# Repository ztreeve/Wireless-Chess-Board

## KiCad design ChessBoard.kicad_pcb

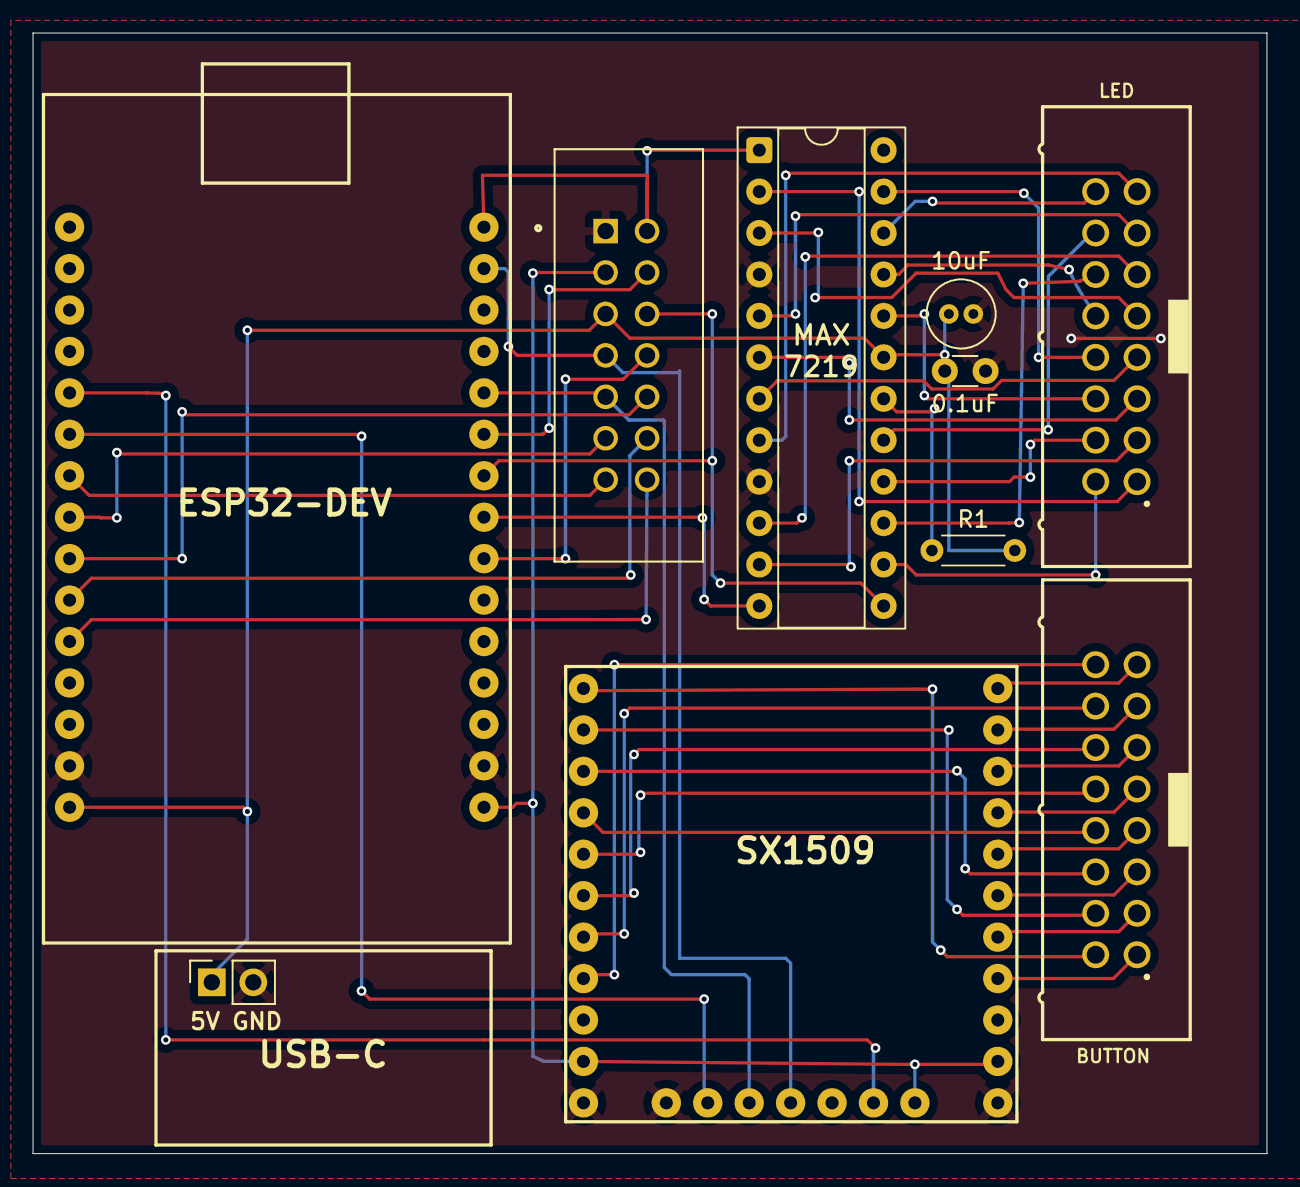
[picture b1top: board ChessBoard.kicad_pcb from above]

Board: 2 copper layers, 75.6 x 68.7 mm, 10 parts (0 on the bottom side), 50 nets.

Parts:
0.1uF: 0.1uF; C_Disc_D3.0mm_W1.6mm_P2.50mm
10uF: 10uF; C_Radial_D4.0mm_H5.0mm_P1.50mm
BUTTON: 16PIN HEADER; 61201621621
J1: SBH11-PBPC-D07-ST-BK; SULLINS_SBH11-PBPC-D07-ST-BK
J2: 6120XX21621_61201621621; 61201621621
J3: USBC BREAKOUT PINS; PinSocket_1x02_P2.54mm_Vertical
R1: 17k; R_Axial_DIN0204_L3.6mm_D1.6mm_P5.08mm_Horizontal
U1: ESP32_DEVKIT_V1_30PIN
U2: SX1509 BREAKOUT
U3: MAX7219; DIP-24_W7.62mm_Socket

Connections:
+3V3: J1.3, U1.1 (3V3), U2.18 (3.3V3), U2.26 (3.3V2), U2.28 (3.3V)
+5V: 0.1uF.1, 10uF.1, J1.5, J3.1, R1.2, U1.30 (VIN), U3.19 (V+)
/A0: BUTTON.1, U2.1 (0)
/A1: BUTTON.3, U2.2 (1)
/A2: BUTTON.5, U2.3 (2)
/A3: BUTTON.7, U2.4 (3)
/A4: BUTTON.9, U2.5 (4)
/A5: BUTTON.11, U2.6 (5)
/A6: BUTTON.13, U2.7 (6)
/A7: BUTTON.15, U2.8 (7)
/B0: BUTTON.2, U2.9 (8)
/B1: BUTTON.4, U2.10 (9)
/B2: BUTTON.6, U2.11 (10)
/B3: BUTTON.8, U2.12 (11)
/B4: BUTTON.10, U2.13 (12)
/B5: BUTTON.12, U2.14 (13)
/B6: BUTTON.14, U2.15 (14)
/B7: BUTTON.16, U2.16 (15)
/CLK: J1.6, U1.9 (D18), U3.13 (CLK)
/CS_1: U1.8 (D5), U3.12 (LOAD)
/CS_2: J1.8, U1.7 (D17)
/D14: J1.14, U1.26 (D14)
/D25: J1.11, U1.23 (D25)
/D26: J1.10, U1.24 (D26)
/D27: J1.12, U1.25 (D27)
/D33: J1.13, U1.22 (D33)
/DIG0: J2.1, U3.2 (DIG_0)
/DIG1: J2.3, U3.11 (DIG_1)
/DIG2: J2.5, U3.6 (DIG_2)
/DIG3: J2.7, U3.7 (DIG_3)
/DIG4: J2.9, U3.3 (DIG_4)
/DIG5: J2.11, U3.10 (DIG_5)
/DIG6: J2.13, U3.5 (DIG_6)
/DIG7: J2.15, U3.8 (DIG_7)
/INT_SX: U1.20 (D35), U2.25 (nINT)
/MISO: J1.4, U1.10 (D19)
/MOSI: J1.2, U1.15 (D23), U3.1 (DIN)
/RST_SX: U1.21 (D32), U2.21 (nRST)
/SCL: J1.7, U1.14 (D22), U2.23 (SCL)
/SDA: J1.9, U1.11 (D21), U2.22 (SDA)
/SEGA: J2.2, U3.14 (SEG_A)
/SEGB: J2.4, U3.16 (SEG_B)
/SEGC: J2.6, U3.20 (SEG_C)
/SEGD: J2.8, U3.23 (SEG_D)
/SEGE: J2.10, U3.21 (SEG_E)
/SEGF: J2.12, U3.15 (SEG_F)
/SEGG: J2.14, U3.17 (SEG_G)
/SEGH: J2.16, U3.22 (SEG_DP)
GND: 0.1uF.2, 10uF.2, J1.1, J3.2, U1.2 (GND1), U1.29 (GND2), U2.19 (GND3), U2.20 (GND2), U2.27 (GND), U3.4 (GND), U3.9 (GND)
unnamed: R1.1, U3.18 (ISET)
